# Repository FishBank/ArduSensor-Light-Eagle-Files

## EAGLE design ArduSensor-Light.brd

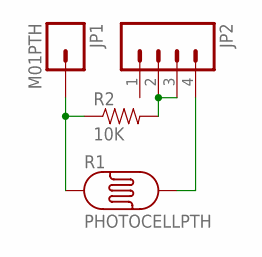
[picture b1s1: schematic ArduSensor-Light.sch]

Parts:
JP1: M01PTH; 1X01
JP2: M04PTH; 1X04
R1: PHOTOCELLPTH; PHOTOCELL
R2: 10K; AXIAL-0.3

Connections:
unnamed: JP1.1, R1.1, R2.P$1 (1)
unnamed: JP2.2, JP2.3, R2.P$2 (2)
unnamed: JP2.4, R1.2

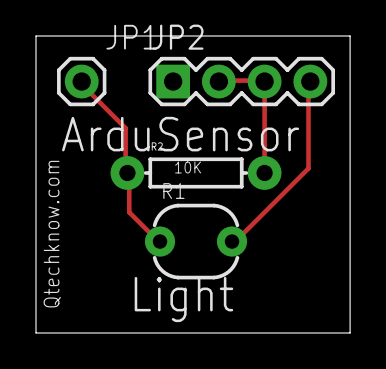
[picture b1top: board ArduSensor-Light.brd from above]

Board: 2 copper layers, 17.4 x 16.5 mm, 4 parts (0 on the bottom side), 3 nets.

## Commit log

2012-07-13 Schematic

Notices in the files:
parts and their libraries:
SFE Connectors: Licensing: CC v3.0 Share-Alike You are welcome to use this library for commercial purposes.
